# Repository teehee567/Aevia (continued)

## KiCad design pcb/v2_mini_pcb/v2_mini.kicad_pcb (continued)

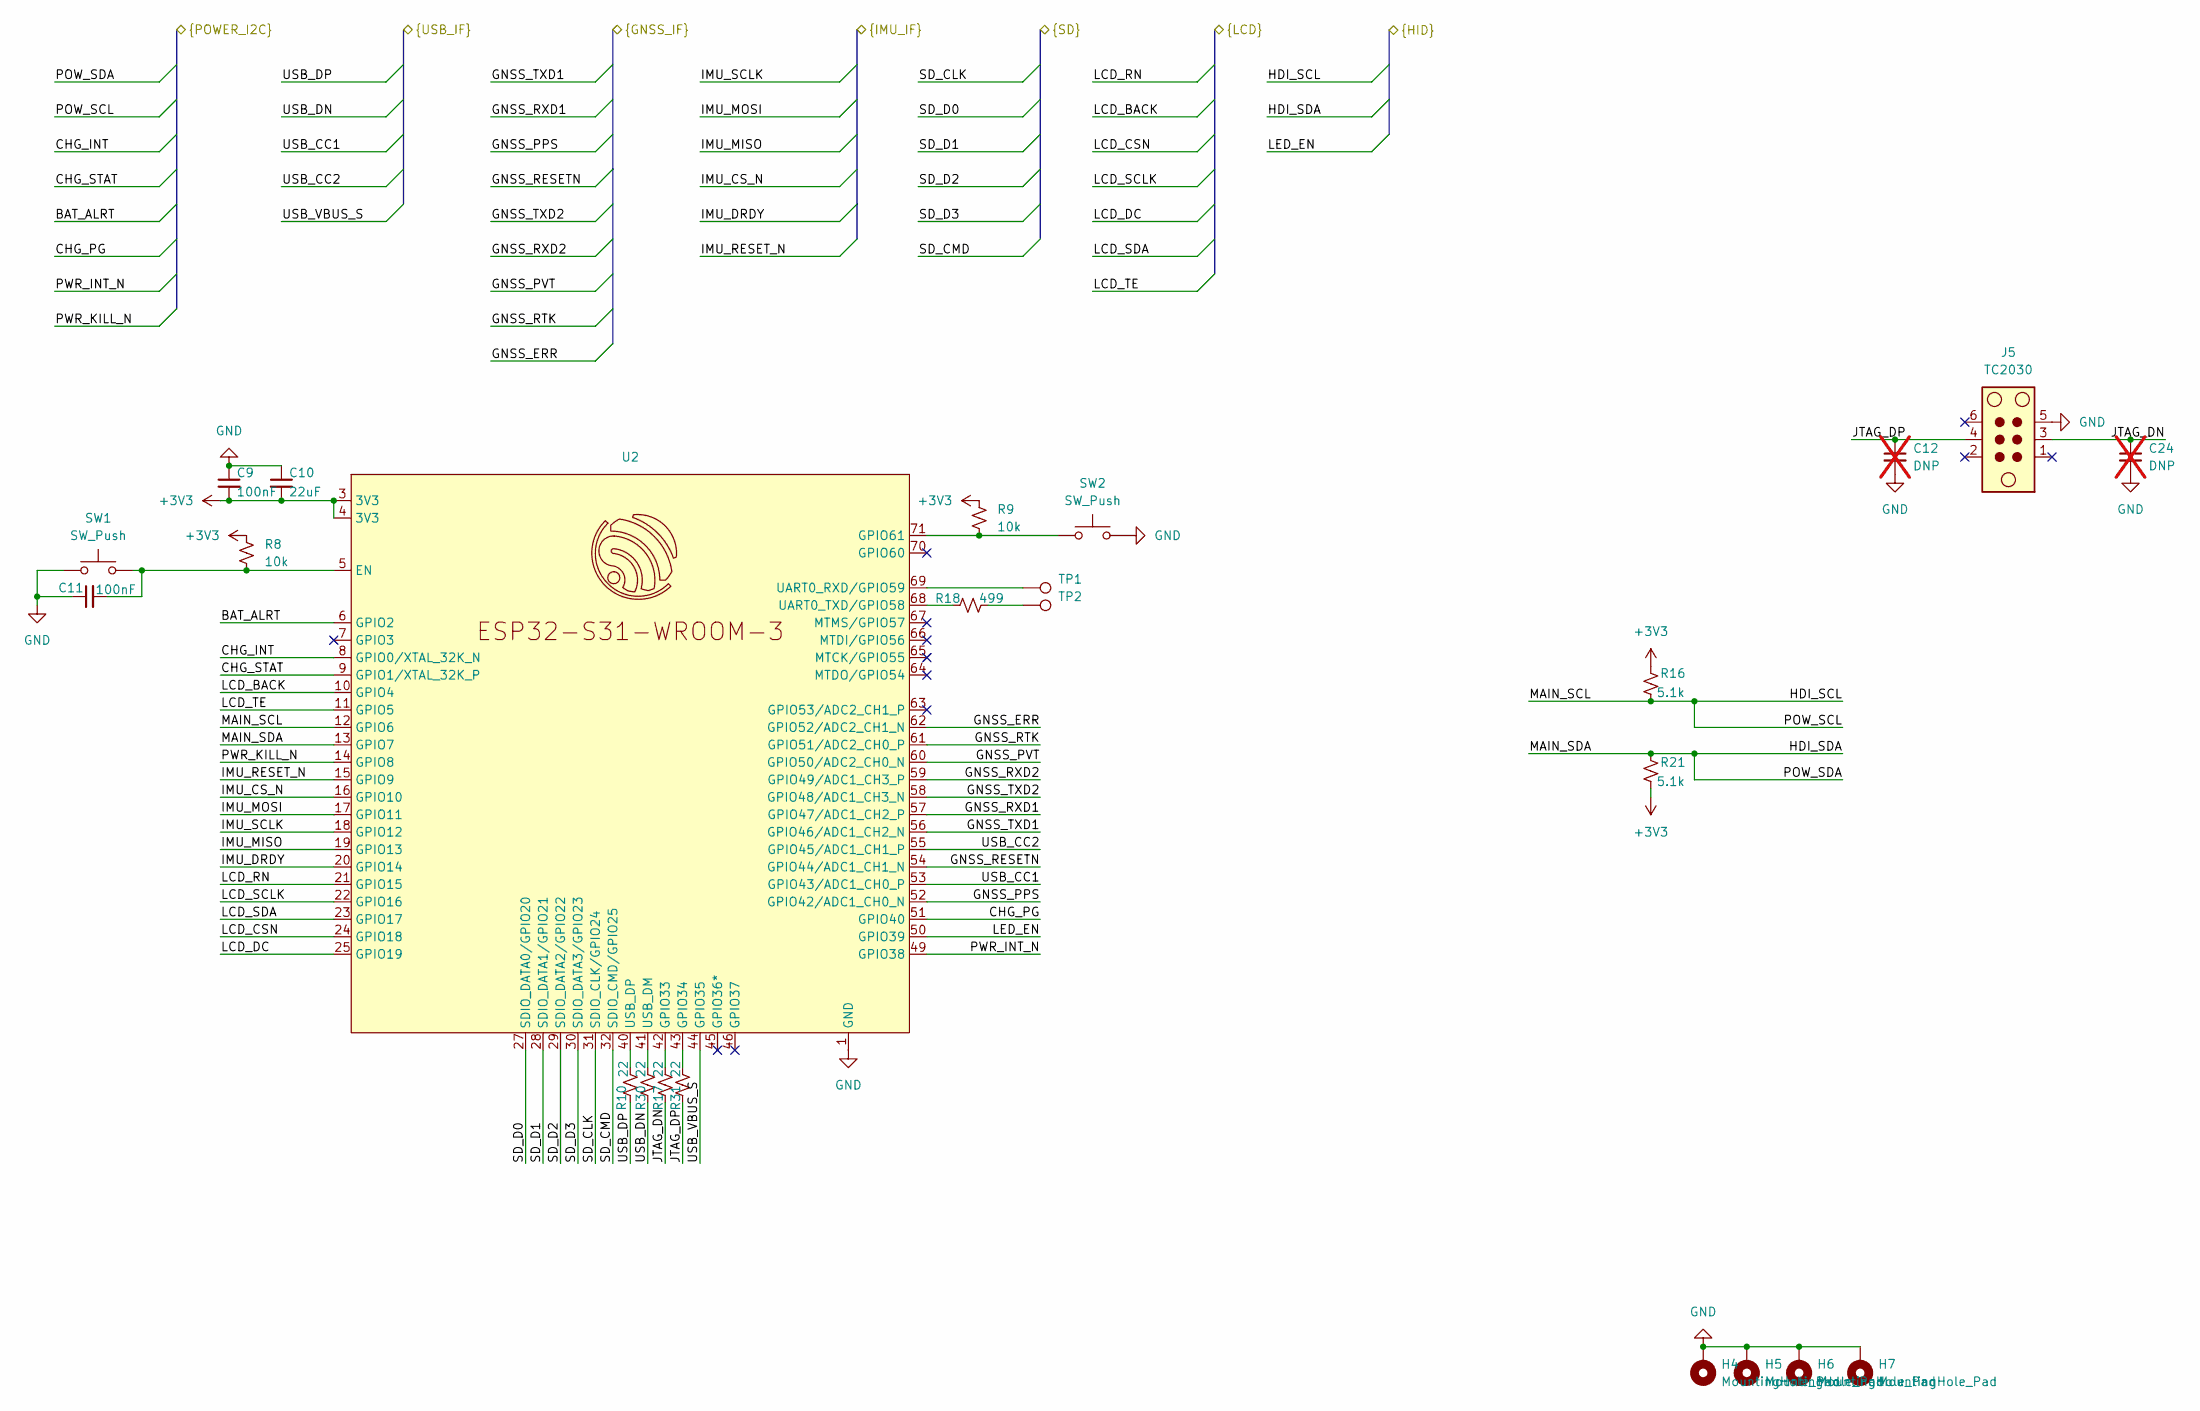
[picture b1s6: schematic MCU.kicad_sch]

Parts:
C9, C11: 100nF; C_0402_1005Metric; Voltage 16V; Tolerance 10%; MPN CL05B104KO5NNNC; LCSC C1525
C10: 22uF; C_0805_2012Metric; Voltage 25V; Tolerance 20%; MPN CC0805MKX5R8BB226; DigiKey_PN 311-1903-1-ND
C12, C24: DNP; C_0402_1005Metric; MPN DNP; not fitted
H4, H5, H6, H7: MountingHole_Pad; MountingHole_2.2mm_M2_Pad
J5: TC2030; Tag-Connect_TC2030-IDC-NL_2x03_P1.27mm_Vertical; MPN TC2030-IDC-NL (mating cable)
R8, R9: 10k; R_0402_1005Metric; Voltage 50V; Tolerance 1%; MPN RC0402FR-0710KL; DigiKey_PN 311-10.0KLRCT-ND
R10, R17, R30, R31: 22; R_0402_1005Metric; Voltage 50V; Tolerance 1%; MPN RC0402FR-0722RL; DigiKey_PN 311-22.0LRCT-ND
R16, R21: 5.1k; R_0402_1005Metric; Voltage 50V; Tolerance 1%; MPN RC0402FR-075K1L; DigiKey_PN 311-5.10KLRCT-ND
R18: 499; R_0402_1005Metric; MPN RC0402FR-07499RL
SW1, SW2: SW_Push; SW_SPST_B3U-1000P; MPN B3U-1000P
TP1, TP2: TestPoint; TestPoint_Pad_D1.0mm; MPN N/A (PCB test pad)
U2: ESP32-S31-WROOM-3; MPN ESP32-S31-WROOM-3-N16R16V

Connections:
+3V3: C9.2, C10.2, R8.1, R9.1, R16.1, R21.2, U2.3 (3V3), U2.4 (3V3); also elsewhere on the board
/ESP32-S31 MCU/BAT_ALRT: U2.6 (GPIO2); also elsewhere on the board
/ESP32-S31 MCU/CHG_INT: U2.8 (GPIO0/XTAL_32K_N); also elsewhere on the board
/ESP32-S31 MCU/CHG_PG: U2.51 (GPIO40); also elsewhere on the board
/ESP32-S31 MCU/CHG_STAT: U2.9 (GPIO1/XTAL_32K_P); also elsewhere on the board
/ESP32-S31 MCU/GNSS_ERR: U2.62 (GPIO52/ADC2_CH1_N); also elsewhere on the board
/ESP32-S31 MCU/GNSS_PPS: U2.52 (GPIO42/ADC1_CH0_N); also elsewhere on the board
/ESP32-S31 MCU/GNSS_PVT: U2.60 (GPIO50/ADC2_CH0_N); also elsewhere on the board
/ESP32-S31 MCU/GNSS_RESETN: U2.54 (GPIO44/ADC1_CH1_N); also elsewhere on the board
/ESP32-S31 MCU/GNSS_RTK: U2.61 (GPIO51/ADC2_CH0_P); also elsewhere on the board
/ESP32-S31 MCU/GNSS_RXD1: U2.57 (GPIO47/ADC1_CH2_P); also elsewhere on the board
/ESP32-S31 MCU/GNSS_RXD2: U2.59 (GPIO49/ADC1_CH3_P); also elsewhere on the board
/ESP32-S31 MCU/GNSS_TXD1: U2.56 (GPIO46/ADC1_CH2_N); also elsewhere on the board
/ESP32-S31 MCU/GNSS_TXD2: U2.58 (GPIO48/ADC1_CH3_N); also elsewhere on the board
/ESP32-S31 MCU/IMU_CS_N: U2.16 (GPIO10); also elsewhere on the board
/ESP32-S31 MCU/IMU_DRDY: U2.20 (GPIO14); also elsewhere on the board
/ESP32-S31 MCU/IMU_MISO: U2.19 (GPIO13); also elsewhere on the board
/ESP32-S31 MCU/IMU_MOSI: U2.17 (GPIO11); also elsewhere on the board
/ESP32-S31 MCU/IMU_RESET_N: U2.15 (GPIO9); also elsewhere on the board
/ESP32-S31 MCU/IMU_SCLK: U2.18 (GPIO12); also elsewhere on the board
/ESP32-S31 MCU/JTAG_DN: C24.1, J5.3, R30.2
/ESP32-S31 MCU/JTAG_DP: C12.1, J5.4, R31.2
/ESP32-S31 MCU/LCD_BACK: U2.10 (GPIO4); also elsewhere on the board
/ESP32-S31 MCU/LCD_CSN: U2.24 (GPIO18); also elsewhere on the board
/ESP32-S31 MCU/LCD_DC: U2.25 (GPIO19); also elsewhere on the board
/ESP32-S31 MCU/LCD_RN: U2.21 (GPIO15); also elsewhere on the board
/ESP32-S31 MCU/LCD_SCLK: U2.22 (GPIO16); also elsewhere on the board
/ESP32-S31 MCU/LCD_SDA: U2.23 (GPIO17); also elsewhere on the board
/ESP32-S31 MCU/LCD_TE: U2.11 (GPIO5); also elsewhere on the board
/ESP32-S31 MCU/LED_EN: U2.50 (GPIO39); also elsewhere on the board
/ESP32-S31 MCU/POW_SCL: R16.2, U2.12 (GPIO6); also elsewhere on the board
/ESP32-S31 MCU/POW_SDA: R21.1, U2.13 (GPIO7); also elsewhere on the board
/ESP32-S31 MCU/PWR_INT_N: U2.49 (GPIO38); also elsewhere on the board
/ESP32-S31 MCU/PWR_KILL_N: U2.14 (GPIO8); also elsewhere on the board
/ESP32-S31 MCU/SD_CLK: U2.31 (SDIO_CLK/GPIO24); also elsewhere on the board
/ESP32-S31 MCU/SD_CMD: U2.32 (SDIO_CMD/GPIO25); also elsewhere on the board
/ESP32-S31 MCU/SD_D0: U2.27 (SDIO_DATA0/GPIO20); also elsewhere on the board
/ESP32-S31 MCU/SD_D1: U2.28 (SDIO_DATA1/GPIO21); also elsewhere on the board
/ESP32-S31 MCU/SD_D2: U2.29 (SDIO_DATA2/GPIO22); also elsewhere on the board
/ESP32-S31 MCU/SD_D3: U2.30 (SDIO_DATA3/GPIO23); also elsewhere on the board
/ESP32-S31 MCU/USB_CC1: U2.53 (GPIO43/ADC1_CH0_P); also elsewhere on the board
/ESP32-S31 MCU/USB_CC2: U2.55 (GPIO45/ADC1_CH1_P); also elsewhere on the board
/ESP32-S31 MCU/USB_DN: R17.2; also elsewhere on the board
/ESP32-S31 MCU/USB_DP: R10.2; also elsewhere on the board
/ESP32-S31 MCU/USB_VBUS_S: U2.44 (GPIO35); also elsewhere on the board
GND: C9.1, C10.1, C11.1, C12.2, C24.2, H4.1 (1_1), H5.1 (1_1), H6.1 (1_1), H7.1 (1_1), J5.5, SW1.1, SW2.2, U2.1 (GND), U2.2 (GND), U2.26 (GND), U2.47 (GND), U2.48 (GND), U2.72 (GND), U2.73 (GND), U2.74 (GND), U2.75 (GND), U2.76 (GND), U2.77 (GND), U2.78 (GND), U2.79 (GND), U2.80 (GND), U2.81 (GND), U2.82 (GND), U2.83 (GND), U2.84 (GND), U2.85 (GND), U2.86 (GND), U2.87 (GND), U2.88 (GND), U2.89 (GND), U2.90 (GND), U2.92 (GND), U2.93 (GND), U2.94 (GND), U2.95 (GND), U2.96 (GND), U2.97 (GND), U2.98 (GND), U2.99 (GND); also elsewhere on the board
unnamed: R18.2, TP2.1 (1_1)
unnamed: C11.2, R8.2, SW1.2, U2.5 (EN)
unnamed: R30.1, U2.42 (GPIO33)
unnamed: R31.1, U2.43 (GPIO34)
unnamed: R9.2, SW2.1, U2.71 (GPIO61)
unnamed: TP1.1 (1_1), U2.69 (UART0_RXD/GPIO59)
unnamed: R18.1, U2.68 (UART0_TXD/GPIO58)
unnamed: R17.1, U2.41 (USB_DM)
unnamed: R10.1, U2.40 (USB_DP)

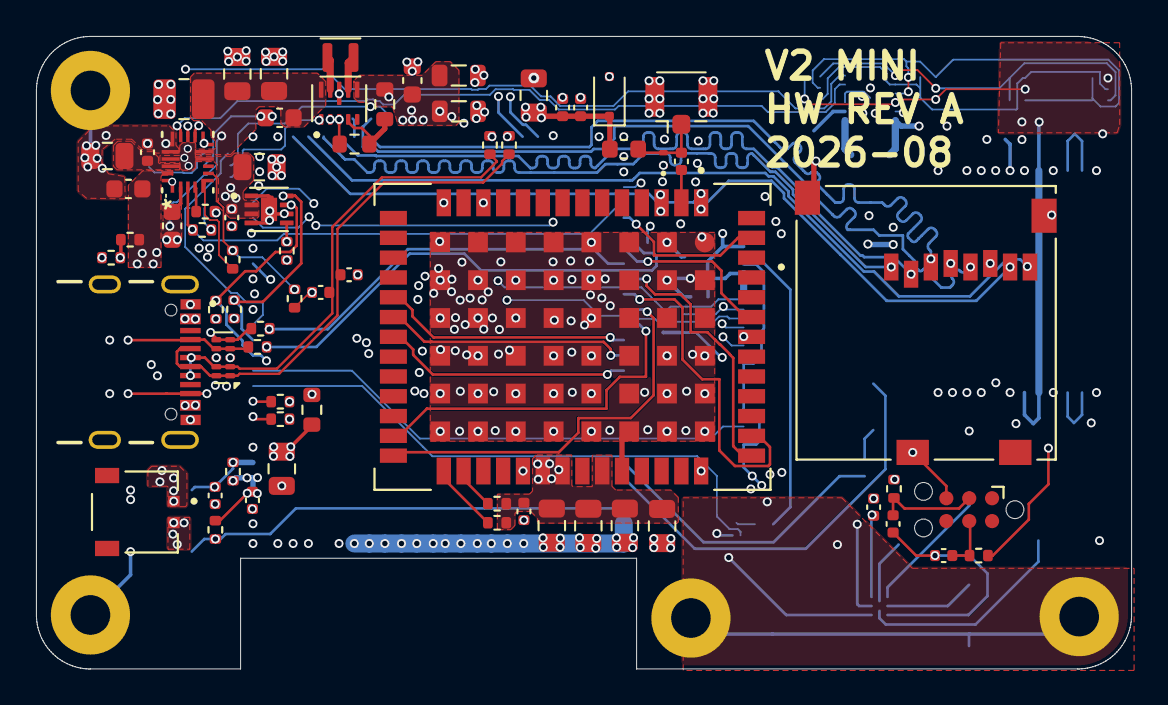
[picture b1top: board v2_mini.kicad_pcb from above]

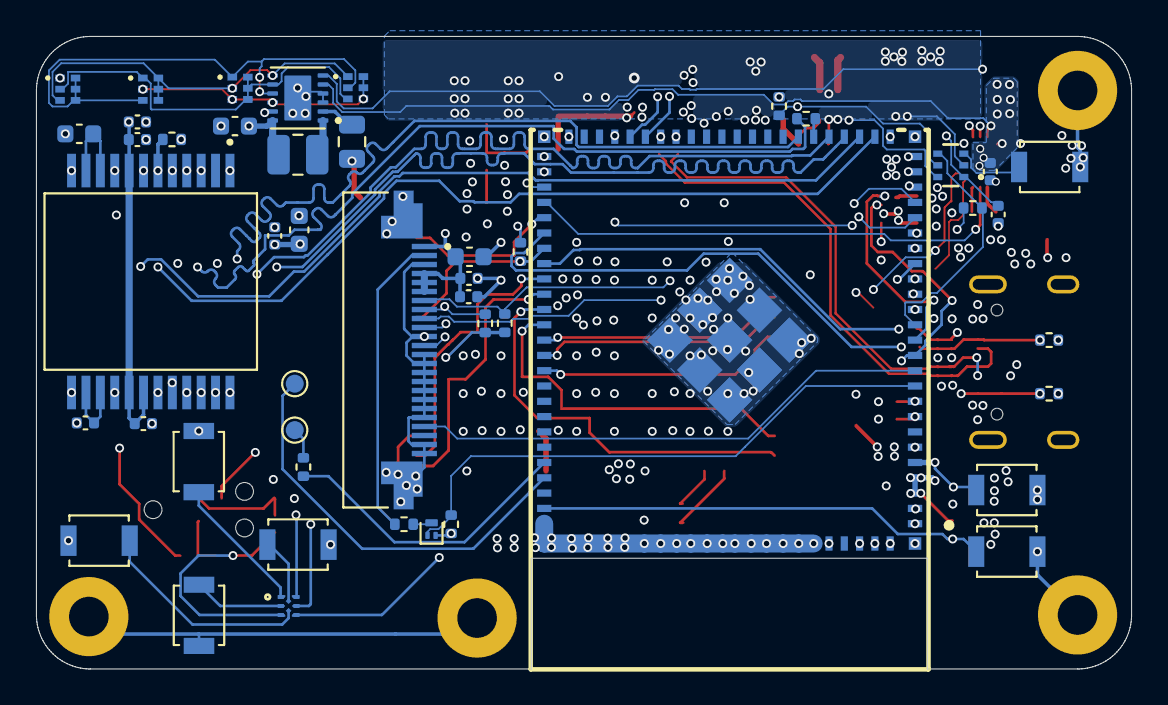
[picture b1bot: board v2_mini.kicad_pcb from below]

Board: 6 copper layers, 60.8 x 35.1 mm, 119 parts (47 on the bottom side), 93 nets.

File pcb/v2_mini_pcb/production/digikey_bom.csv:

Quantity,Digi-Key Part Number,Manufacturer Part Number,Manufacturer,Customer Reference,Value,Footprint
2,490-5922-1-ND,GRM1555C1H101JA01D,Murata Electronics,"C1,C3",100pF,Capacitor_SMD:C_0402_1005Metric
12,,CL05B104KO5NNNC,Samsung Electro-Mechanics,"C2,C8,C9,C11,C13,C15,C21,C22,C29,C38,C40,C41",100nF,Capacitor_SMD:C_0402_1005Metric
6,445-14418-1-ND,C2012X5R1V106K125AC,TDK,"C4,C5,C6,C7,C20,C35",10uF,Capacitor_SMD:C_0805_2012Metric
5,311-1903-1-ND,CC0805MKX5R8BB226,YAGEO,"C10,C28,C30,C31,C32",22uF,Capacitor_SMD:C_0805_2012Metric
5,1276-CL10A106KP8NNNDCT-ND,CL10A106KP8NNND,Samsung Electro-Mechanics,"C14,C23,C27,C33,C36",10uF,Capacitor_SMD:C_0603_1608Metric
1,587-MCASG168AB7105KTNA01CT-ND,MCASG168AB7105KTNA01,Taiyo Yuden,C16,1uF,Capacitor_SMD:C_0603_1608Metric
1,490-3254-1-ND,GRM155R71E473KA88D,Murata Electronics,C17,47nF,Capacitor_SMD:C_0402_1005Metric
1,490-7203-1-ND,GRM188R61E475KE11D,Murata Electronics,C18,4.7uF,Capacitor_SMD:C_0603_1608Metric
1,,CL05B104KB54PNC,Samsung Electro-Mechanics,C19,100nF,Capacitor_SMD:C_0402_1005Metric
1,490-GRT188R61A226ME13DCT-ND,GRT188R61A226ME13D,Murata Electronics,C34,22uF,Capacitor_SMD:C_0603_1608Metric
2,,CL05A105KA5NQNC,Samsung Electro-Mechanics,"C37,C39",1uF,Capacitor_SMD:C_0402_1005Metric
1,,TPD1E0B04DPYR,,D1,~,Package_SON:Texas_DPY0002A_0.6x1mm_P0.65mm
1,,ESDS311DYFR,,D2,~,Diode_SMD:D_SOD-323F
4,,MSL0402RGBU1,,"D32,D33,D34,D35",MSL0402RGBU1,all:LED_MSL04_ROM
2,,MPZ2012S601ATD25,,"FB1,FB2",BLM21SP601SN1D,Inductor_SMD:L_0805_2012Metric
1,,U.FL-R-SMT-1(01),,J1,Conn_Coaxial,all:U.FL_Hirose_U.FL-R-SMT-1_Vertical
1,,GTFP08441BEU,Amphenol,J2,GTFP08441BEU,all:AMPHENOL_GTFP08441BEU
1,,SFV24R-2STE1HLF,Amphenol,J3,SFV24R-2STE1HLF,all:AMPHENOL_SFV24R-2STE1HLF
1,,DF58-2P-1.2V(21),,J4,Battery,all:HRS_DF58-2P-1.2V_21_
1,,USB4105-GF-A,GCT,J6,USB4105-GF-A,all:GCT_USB4105-GF-A
1,,LQW18AN68NJ00D,,L1,68nH,Inductor_SMD:L_0603_1608Metric
2,,DFE252012F-1R0M=P2,,"L2,L4",1uH,Inductor_SMD:L_1008_2520Metric
1,1276-6902-1-ND,CIGT201610EHR47MNE,Samsung Electro-Mechanics,L5,0.47uH,all:L_Samsung_CIGT201610
1,,NTNS3164NZT5G,,Q1,NTNS3164NZT5G,Package_TO_SOT_SMD:SOT-883
14,311-10.0KLRCT-ND,RC0402FR-0710KL,YAGEO,"R1,R2,R3,R6,R7,R8,R9,R20,R22,R23,R24,R27,R34,R35",10k,Resistor_SMD:R_0402_1005Metric
1,,RC0402FR-0715RL,,R4,15,Resistor_SMD:R_0402_1005Metric
2,311-100KLRCT-ND,RC0402FR-07100KL,YAGEO,"R5,R29",100k,Resistor_SMD:R_0402_1005Metric
5,311-22.0LRCT-ND,RC0402FR-0722RL,YAGEO,"R10,R17,R19,R30,R31",22,Resistor_SMD:R_0402_1005Metric
4,311-5.10KLRCT-ND,RC0402FR-075K1L,YAGEO,"R11,R12,R16,R21",5.1k,Resistor_SMD:R_0402_1005Metric
1,,RC0402FR-075K62L,,R13,5.62k,Resistor_SMD:R_0402_1005Metric
1,,RC0402FR-075K23L,,R14,5.23k,Resistor_SMD:R_0402_1005Metric
1,,CRCW040230K1FKED,,R15,30.1k,Resistor_SMD:R_0402_1005Metric
1,,RC0402FR-07499RL,,R18,499,Resistor_SMD:R_0402_1005Metric
1,,RC0603FR-07511KL,,R25,511k,Resistor_SMD:R_0603_1608Metric
1,,RC0603FR-0791KL,,R26,91k,Resistor_SMD:R_0603_1608Metric
1,RMCF0402FT75K0CT-ND,RMCF0402FT75K0,Stackpole Electronics Inc,R28,75k,Resistor_SMD:R_0402_1005Metric
2,311-22.0KLRCT-ND,RC0402FR-0722KL,YAGEO,"R32,R33",22k,Resistor_SMD:R_0402_1005Metric
7,,B3U-1000P,,"SW1,SW2,SW3,SW4,SW5,SW6,SW7",SW_Push,Button_Switch_SMD:SW_SPST_B3U-1000P
1,,NCU18XH103F60RB,,TH1,103KT1608T-1P,Resistor_SMD:R_0603_1608Metric
1,,UM980,Unicore Comm,U1,UM980,all:XCVR_UM980
1,,ESP32-S31-WROOM-3-N16R16V,,U2,~,all:ESP32-S31-WROOM-3
1,,SCH16T-K01-1,Murata,U3,SCH16T-K01-1,all:XDCR_SCH16T-K01-1
1,,LP5813ADRRR,Texas Instruments,U4,LP5813ADRRR,all:IC_LP5813ADRRR
1,,TCA9536ADTMR,,U5,TCA9536ADTMR,all:X2SON8_DTM_TEX
1,,TPD4EUSB30DQAR,,U6,TPD4EUSB30,Package_SON:USON-10_2.5x1.0mm_P0.5mm
1,,MAX16169AALTA+T,,U7,MAX16169AALTA+T,all:21-0164_L622&plus_1_ADI
1,,BQ25622ERYKR,,U8,BQ25622ERYKR,all:WQFN-HR18__RYK_TEX
1,,MAX17048G+T10,,U9,MAX17048G_T10,all:SON50P200X200X80-9N
1,,TPS63802DLAR,Texas Instruments,U10,TPS63802DLAR,all:VREG_TPS63802DLAR

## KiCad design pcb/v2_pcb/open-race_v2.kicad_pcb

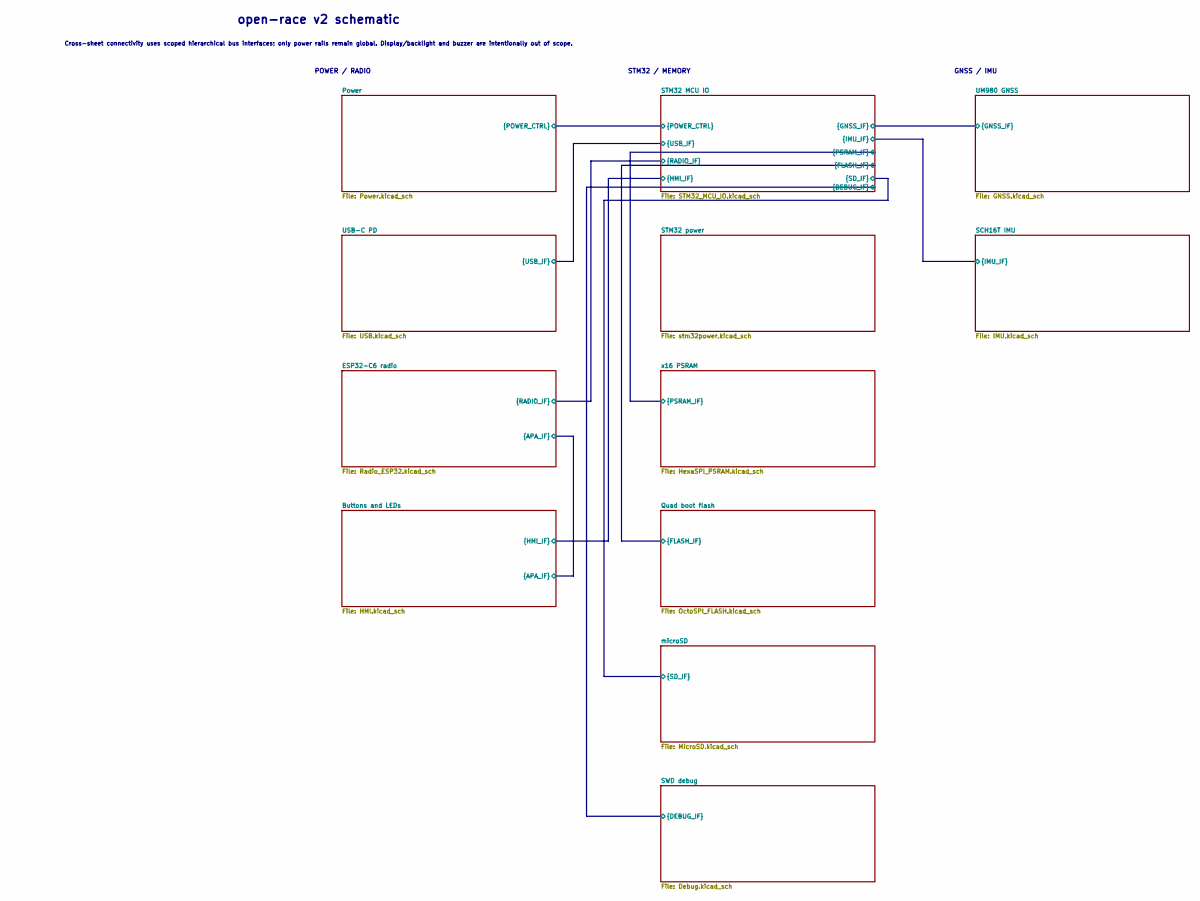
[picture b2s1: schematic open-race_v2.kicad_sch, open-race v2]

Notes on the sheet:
GNSS / IMU
STM32 / MEMORY
Cross-sheet connectivity uses scoped hierarchical bus interfaces; only power rails remain global. Display/backlight and buzzer are intentionally out of scope.
open-race v2 schematic
POWER / RADIO

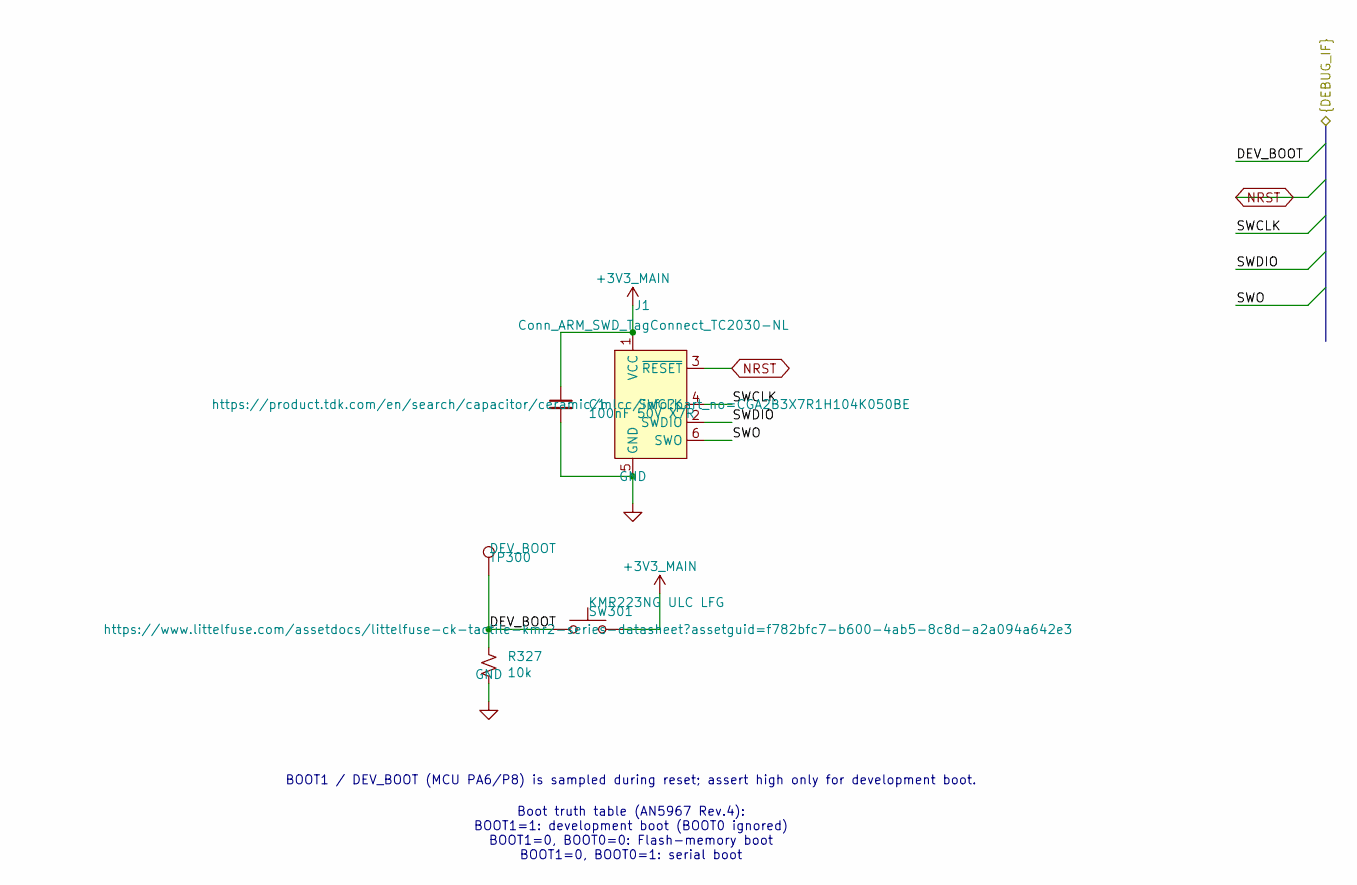
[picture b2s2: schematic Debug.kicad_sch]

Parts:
C1: 100nF 50V X7R; C_0402_1005Metric; Voltage 50 VDC; Tolerance ±10%; MPN CGA2B3X7R1H104K050BE
J1: Conn_ARM_SWD_TagConnect_TC2030-NL; Tag-Connect_TC2030-IDC-NL_2x03_P1.27mm_Vertical
R327: 10k; R_0402_1005Metric; Tolerance ±1%; MPN CRCW040210K0FKED
SW301: KMR223NG ULC LFG; SW_Push_1P1T_NO_CK_KMR2; MPN Y78B22324FP
TP300: DEV_BOOT; TestPoint_Plated_Hole_D2.0mm

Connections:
/STM32 MCU IO/DEV_BOOT: R327.1, SW301.1, TP300.1 (1_1); also elsewhere on the board
/STM32 MCU IO/SWCLK: J1.4 (SWCLK); also elsewhere on the board
/STM32 MCU IO/SWDIO: J1.2 (SWDIO); also elsewhere on the board
/STM32 MCU IO/SWO: J1.6 (SWO); also elsewhere on the board
NRST: J1.3 (~RESET); also elsewhere on the board

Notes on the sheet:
BOOT1 / DEV_BOOT (MCU PA6/P8) is sampled during reset; assert high only for development boot.
Boot truth table (AN5967 Rev.4): BOOT1=1: development boot (BOOT0 ignored) BOOT1=0, BOOT0=0: Flash-memory boot BOOT1=0, BOOT0=1: serial boot

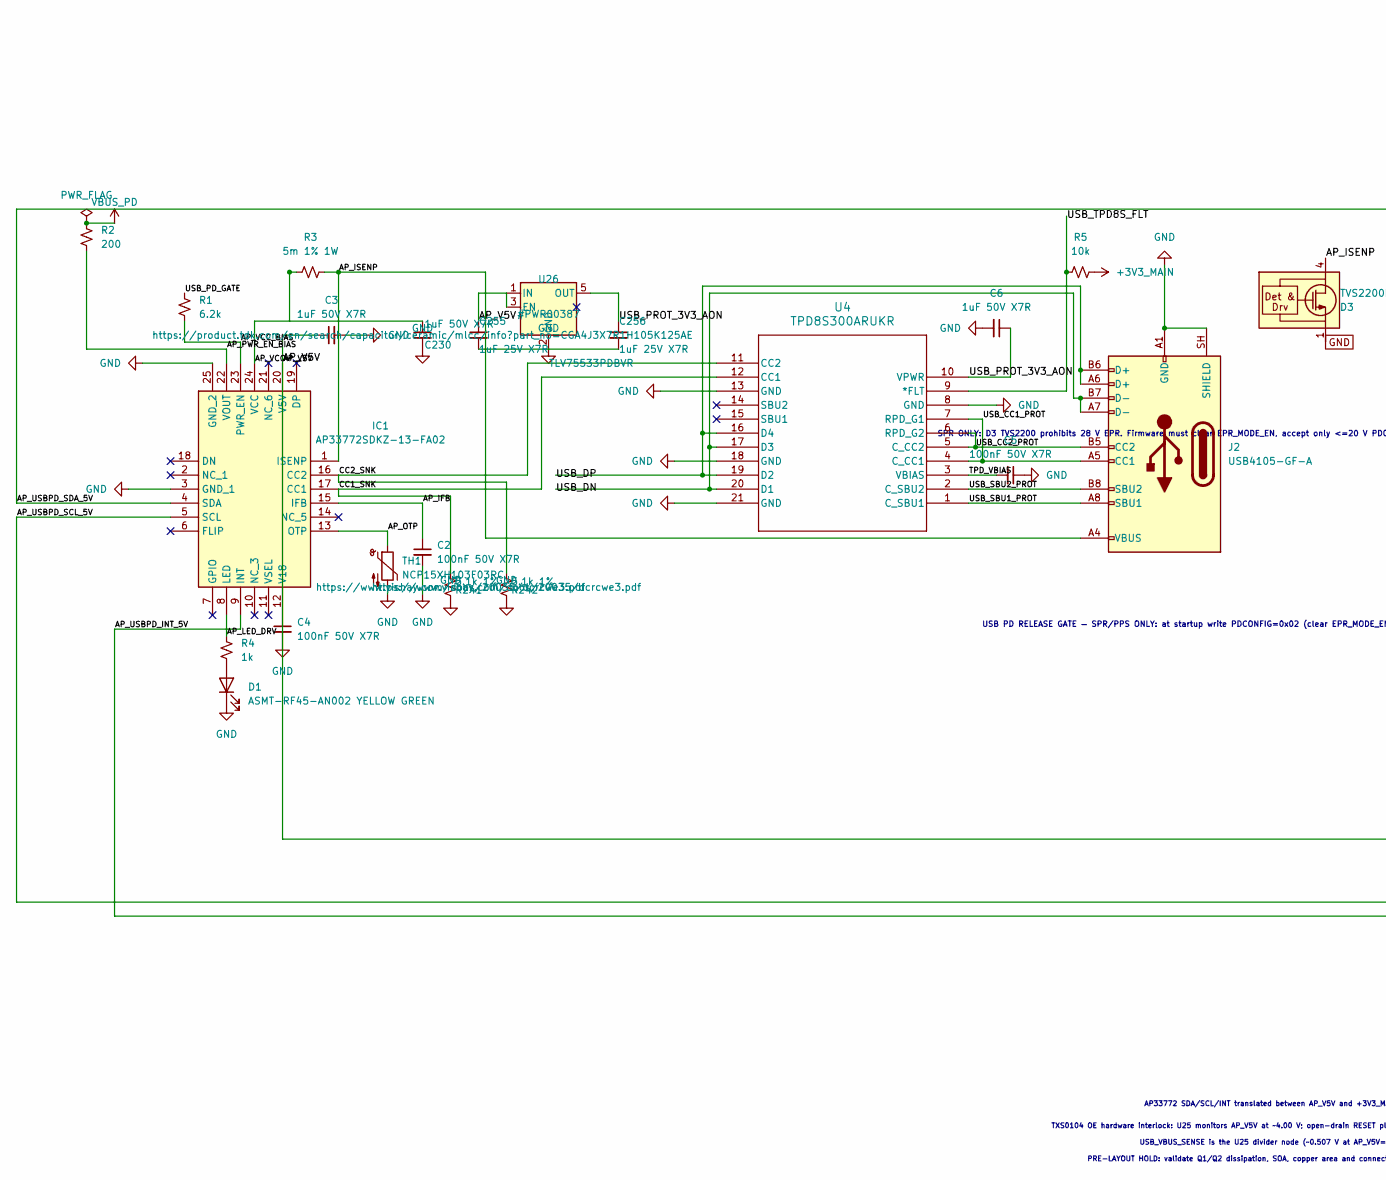
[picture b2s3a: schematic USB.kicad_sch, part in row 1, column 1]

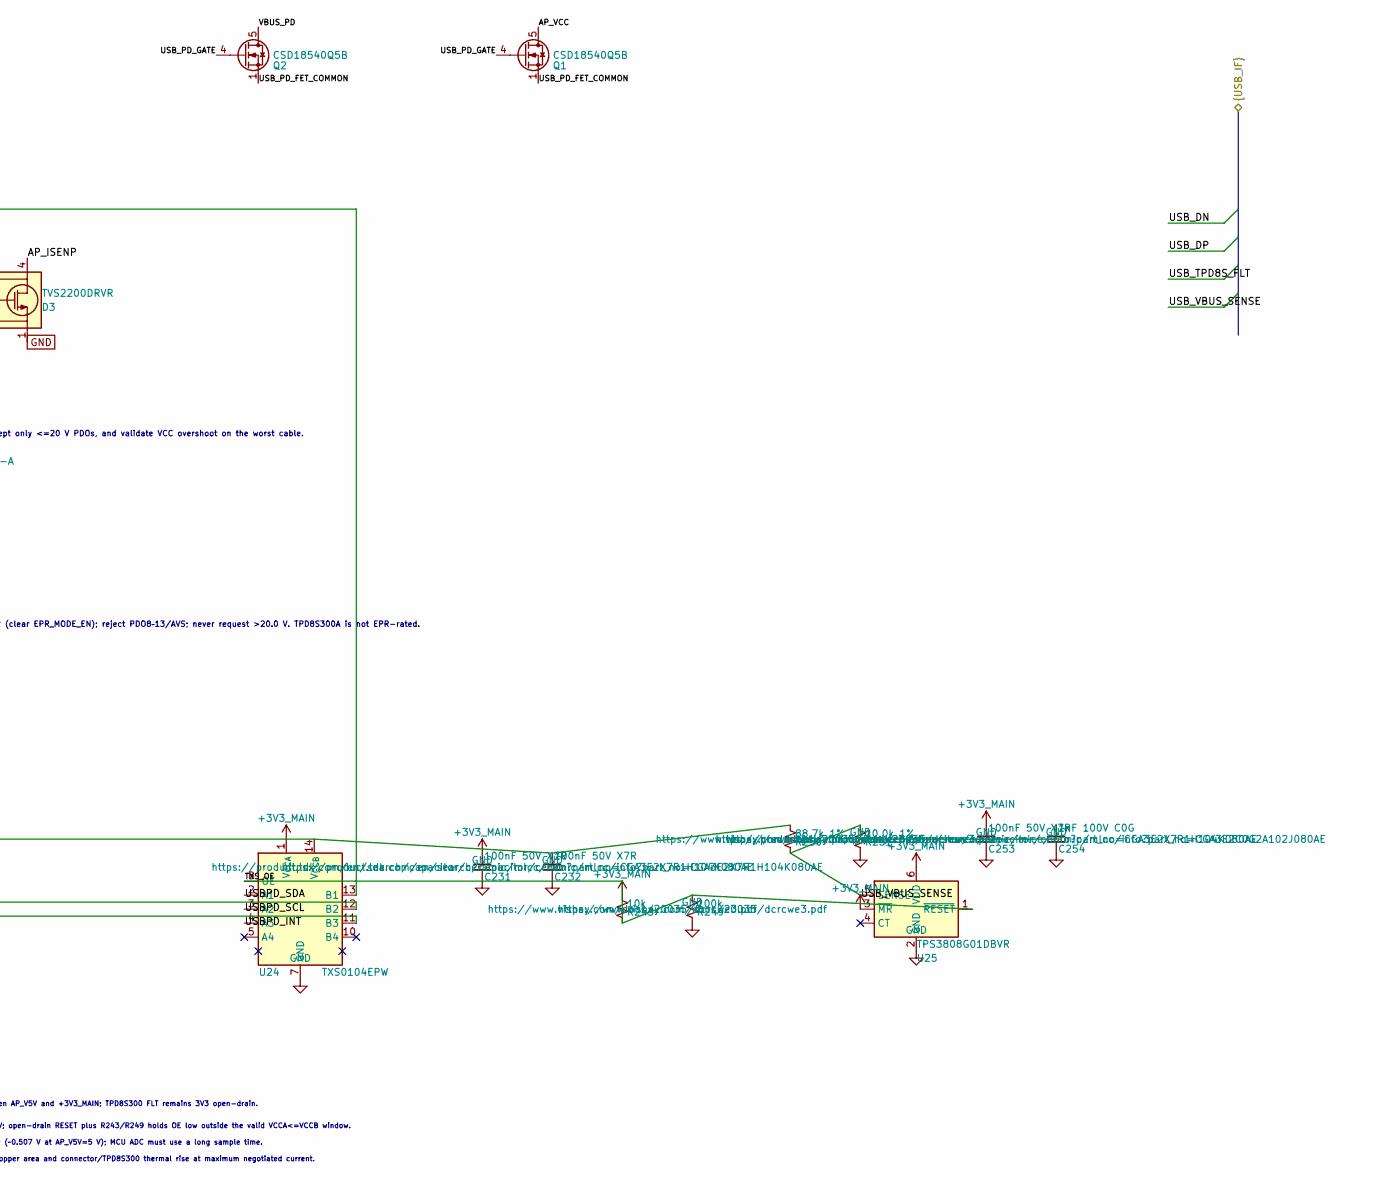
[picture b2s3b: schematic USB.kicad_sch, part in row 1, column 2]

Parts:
C2, C4, C5, C231, C232, C253: 100nF 50V X7R; C_0603_1608Metric; Voltage 50 VDC; Tolerance ±10%; MPN CGA3E2X7R1H104K080AE
C3, C6, C230: 1uF 50V X7R; C_0805_2012Metric; Voltage 50 VDC; Tolerance ±10%; MPN CGA4J3X7R1H105K125AE
C254: 1nF 100V C0G; C_0603_1608Metric; Voltage 100 VDC; Tolerance ±5%; MPN CGA3E2C0G2A102J080AE
C255, C256: 1uF 25V X7R; C_0603_1608Metric; Voltage 25 VDC; Tolerance ±10%; MPN CGA3E1X7R1E105K080AE
D1: ASMT-RF45-AN002 YELLOW GREEN; LED_0603_1608Metric; MPN ASMT-RF45-AN002
D3: TVS2200DRVR; WSON-6-1EP_2x2mm_P0.65mm_EP1x1.6mm_TVS2200; MPN TVS2200DRVR
IC1: AP33772SDKZ-13-FA02; WQFN-24-1EP_4x4mm_P0.5mm_EP2.70x2.70mm_AP33772S; Manufacturer_Part_Number AP33772SDKZ-13-FA02
J2: USB4105-GF-A; USB_C_Receptacle_GCT_USB4105-xx-A_16P_TopMnt_Horizontal; MPN USB4105-GF-A
Q1, Q2: CSD18540Q5B; VSON-CLIP-8_DNK_5x6mm; MPN CSD18540Q5B
R1: 6.2k; R_0603_1608Metric; Tolerance ±1%; MPN CRCW06036K20FKEA
R2: 200; R_0603_1608Metric; Tolerance ±1%; MPN CRCW0603200RFKEA
R3: 5m 1% 1W; R_2512_6332Metric; Tolerance ±1%; MPN WSL2512R0050FEA
R4: 1k; R_0603_1608Metric; Tolerance ±1%; MPN CRCW06031K00FKEA
R5, R243: 10k; R_0603_1608Metric; Tolerance ±1%; MPN CRCW060310K0FKEA
R241, R242: 5.1k 1%; R_0603_1608Metric; Tolerance ±1%; MPN CRCW06035K10FKEA
R249: 100k; R_0603_1608Metric; Tolerance ±1%; MPN CRCW0603100KFKEA
R250: 88.7k 1%; R_0603_1608Metric; Tolerance ±1%; MPN CRCW060388K7FKEA
R251: 10.0k 1%; R_0603_1608Metric; Tolerance ±1%; MPN CRCW060310K0FKEA
TH1: NCP15XH103F03RC; R_0402_1005Metric; MPN NCP15XH103F03RC
U4: TPD8S300ARUKR; Texas_RUK0020B_WQFN-20-1EP_3x3mm_P0.4mm_EP1.7x1.7mm; MPN TPD8S300ARUKR
U24: TXS0104EPW; TSSOP-14_4.4x5mm_P0.65mm; MPN TXS0104EPWR
U25: TPS3808G01DBVR; SOT-23-6; MPN TPS3808G01DBVR
U26: TLV75533PDBVR; SOT-23-5; MPN TLV75533PDBVR

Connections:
/STM32 MCU IO/USBPD_INT: U24.4 (A3); also elsewhere on the board
/STM32 MCU IO/USBPD_SCL: U24.3 (A2); also elsewhere on the board
/STM32 MCU IO/USBPD_SDA: U24.2 (A1); also elsewhere on the board
/STM32 MCU IO/USB_DN: J2.A7 (D-), J2.B7 (D-), U4.17 (D3), U4.20 (D1); also elsewhere on the board
/STM32 MCU IO/USB_DP: J2.A6 (D+), J2.B6 (D+), U4.16 (D4), U4.19 (D2); also elsewhere on the board
/STM32 MCU IO/USB_TPD8S_FLT: R5.1, U4.9 (*FLT); also elsewhere on the board
/STM32 MCU IO/USB_VBUS_SENSE: C254.1, R250.2, R251.1, U25.5 (SENSE); also elsewhere on the board
/USB-C PD/AP_IFB: C2.1, IC1.15 (IFB)
/USB-C PD/AP_ISENP: D3.4 (IN), D3.5 (IN), D3.6 (IN), IC1.1 (ISENP), J2.A4 (VBUS), J2.A9 (VBUS), J2.B4 (VBUS), J2.B9 (VBUS), R3.2
/USB-C PD/AP_LED_DRV: IC1.8 (LED), R4.1
/USB-C PD/AP_OTP: IC1.13 (OTP), TH1.1
/USB-C PD/AP_PWR_EN_BIAS: IC1.22 (VOUT), R2.2
/USB-C PD/AP_USBPD_INT_5V: IC1.9 (INT), U24.11 (B3)
/USB-C PD/AP_USBPD_SCL_5V: IC1.5 (SCL), U24.12 (B2)
/USB-C PD/AP_USBPD_SDA_5V: IC1.4 (SDA), U24.13 (B1)
/USB-C PD/AP_VCC: C230.1, IC1.24 (VCC), Q1.5 (D), Q1.6 (D), Q1.7 (D), Q1.8 (D), R3.1
/USB-C PD/AP_VCC_BIAS: IC1.23 (PWR_EN), R1.2
/USB-C PD/CC1_SNK: IC1.17 (CC1), R241.1, U4.12 (CC1)
/USB-C PD/CC2_SNK: IC1.16 (CC2), R242.1, U4.11 (CC2)
/USB-C PD/TPD_VBIAS: C5.2, U4.3 (VBIAS)
/USB-C PD/USB_CC1_PROT: J2.A5 (CC1), U4.4 (C_CC1), U4.7 (RPD_G1)
/USB-C PD/USB_CC2_PROT: J2.B5 (CC2), U4.5 (C_CC2), U4.6 (RPD_G2)
/USB-C PD/USB_PD_FET_COMMON: Q1.1 (S), Q1.2 (S), Q1.3 (S), Q2.1 (S), Q2.2 (S), Q2.3 (S)
/USB-C PD/USB_PD_GATE: Q1.4 (G), Q2.4 (G), R1.1
/USB-C PD/USB_PROT_3V3_AON: C6.1, C256.1, U4.10 (VPWR), U26.5 (OUT)
/USB-C PD/USB_SBU1_PROT: J2.A8 (SBU1), U4.1 (C_SBU1)
/USB-C PD/USB_SBU2_PROT: J2.B8 (SBU2), U4.2 (C_SBU2)
unnamed: D1.2 (A), R4.2
unnamed: C4.1, IC1.12 (V18)
VBUS_PD: Q2.5 (D), Q2.6 (D), Q2.7 (D), Q2.8 (D), R2.1; also elsewhere on the board

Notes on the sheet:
USB PD RELEASE GATE — SPR/PPS ONLY: at startup write PDCONFIG=0x02 (clear EPR_MODE_EN); reject PDO8–13/AVS; never request >20.0 V. TPD8S300A is not EPR-rated.
USB_VBUS_SENSE is the U25 divider node (~0.507 V at AP_V5V=5 V); MCU ADC must use a long sample time.
AP33772 SDA/SCL/INT translated between AP_V5V and +3V3_MAIN; TPD8S300 FLT remains 3V3 open-drain.
PRE-LAYOUT HOLD: validate Q1/Q2 dissipation, SOA, copper area and connector/TPD8S300 thermal rise at maximum negotiated current.
TXS0104 OE hardware interlock: U25 monitors AP_V5V at ~4.00 V; open-drain RESET plus R243/R249 holds OE low outside the valid VCCA<=VCCB window.
SPR ONLY: D3 TVS2200 prohibits 28 V EPR. Firmware must clear EPR_MODE_EN, accept only <=20 V PDOs, and validate VCC overshoot on the worst cable.

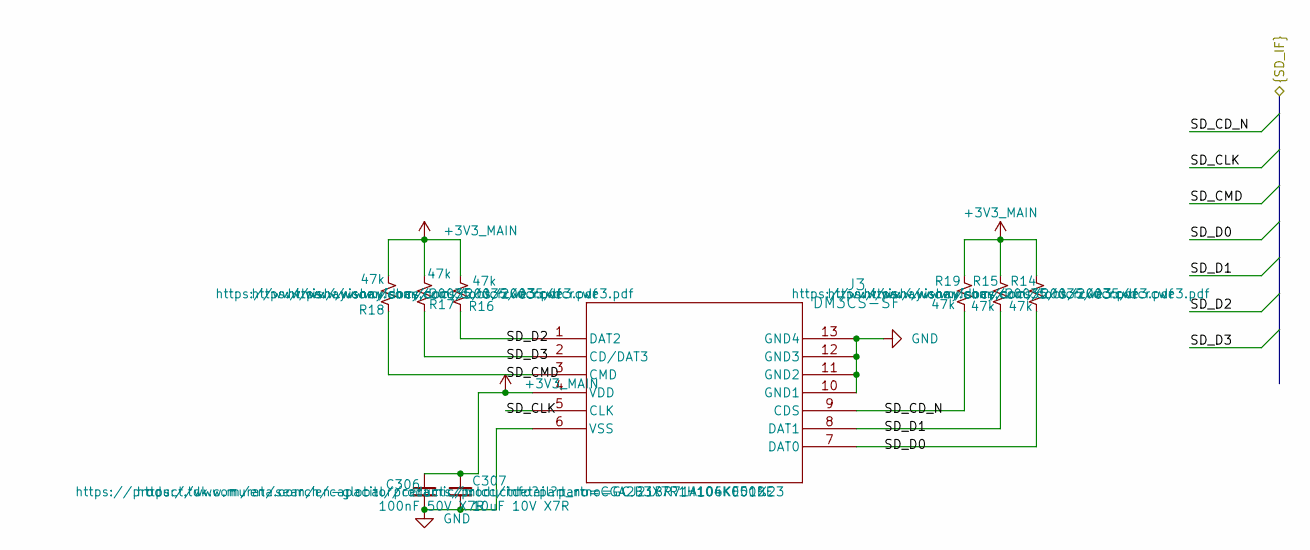
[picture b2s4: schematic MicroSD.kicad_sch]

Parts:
C306: 100nF 50V X7R; C_0402_1005Metric; Voltage 50 VDC; Tolerance ±10%; MPN CGA2B3X7R1H104K050BE
C307: 10uF 10V X7R; C_0805_2012Metric; Voltage 10 VDC; Tolerance ±10%; MPN GCJ21BR71A106KE01L
J3: DM3CS-SF; DM3CS-SF_HIR; MPN DM3CS-SF
R14, R15, R16, R17, R18, R19: 47k; R_0402_1005Metric; Tolerance ±1%; MPN CRCW040247K0FKED

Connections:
/STM32 MCU IO/SD_CD_N: J3.9 (CDS), R19.2; also elsewhere on the board
/STM32 MCU IO/SD_CLK: J3.5 (CLK); also elsewhere on the board
/STM32 MCU IO/SD_CMD: J3.3 (CMD), R18.2; also elsewhere on the board
/STM32 MCU IO/SD_D0: J3.7 (DAT0), R14.2; also elsewhere on the board
/STM32 MCU IO/SD_D1: J3.8 (DAT1), R15.2; also elsewhere on the board
/STM32 MCU IO/SD_D2: J3.1 (DAT2), R16.2; also elsewhere on the board
/STM32 MCU IO/SD_D3: J3.2 (CD/DAT3), R17.2; also elsewhere on the board
